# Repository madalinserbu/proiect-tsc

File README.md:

# OpenBook
Proiect TSC - Serbu Ovidiu Madalin

## Block Diagram

## Components

- **Microcontroller:** ESP32-C6 with integrated Wi-Fi 6 and Bluetooth 5 — responsible for core processing, communication, and power management.
- **Display:** 800×480 resolution e-Paper (e-Ink) display interfaced via SPI — ideal for low-power, high-visibility content rendering.
- **Sensors:** BME688 environmental sensor (temperature, humidity, pressure, air quality) connected through I2C.
- **Power Supply:** 2500mAh LiPo battery with USB-C charging and integrated fuel gauge for real-time battery monitoring.
- **Storage:** MicroSD card slot for storing e-books and other resources, communicating via SPI.
- **Real-Time Clock:** DS3231 RTC module with battery backup for accurate timekeeping even during power loss.
- **User Inputs:** 3 buttons (connected via GPIO) for navigation and control.
- **Expansion Options:** QWIIC/Stemma QT connector for easy integration of additional sensors or modules.

## Bill Of Materials

|                                   name                                   	|        value       	| description                                                           	| quantity 	|                                                                                                                                                     link                                                                                                                                                    	| datasheet                                                                                                                           	|
|:------------------------------------------------------------------------:	|:------------------:	|-----------------------------------------------------------------------	|:--------:	|:-----------------------------------------------------------------------------------------------------------------------------------------------------------------------------------------------------------------------------------------------------------------------------------------------------------:	|-------------------------------------------------------------------------------------------------------------------------------------	|
| LED1                                                                     	|          -         	| LED                                                                   	| 1        	| [link](https://www.niden.ro/led-uri-smd/4560-led-smd-0603-alb-rece.html)                                                                                                                                                                                                                                    	| [link](https://www.mouser.com/datasheet/2/423/LSM0603472V_(1)-1379786.pdf?srsltid=AfmBOoqdcB2pVIrWRImdZdFZcxn5SIjNLKeNM1u-ULY7G7UgiZHJYMAt)	|
| C18                                                                      	|      0.1uF/50V     	| CAPACITOR, European symbol                                            	| 1        	| [link](https://ro.mouser.com/ProductDetail/KEMET/C0402C104K4RAC7411?qs=GedzDrHbfJPMv36lRRfk4g%3D%3D)                                                                                                                                                                                                                	| [link](https://ro.mouser.com/datasheet/2/447/KEM_C1002_X7R_SMD-3316098.pdf)                                                                 	|
| R5                                                                       	|        0.47        	| RESISTOR, European symbol                                             	| 1        	| [link](https://ro.mouser.com/ProductDetail/ROHM-Semiconductor/SFR01MZPJ471?qs=sGAEpiMZZMtlubZbdhIBIONtIqra%2FA5YbUieG7R0owU%3D)                                                                                                                                                                                     	| [link](https://fscdn.rohm.com/en/products/databook/datasheet/passive/resistor/chip_resistor/sfr-e.pdf)                                      	|
| R1                                                                       	|        100K        	| RESISTOR, European symbol                                             	| 1        	| [link](https://ro.mouser.com/ProductDetail/Bourns/CR0402-FX-1003GLF?qs=URDPQ%2Fj0cz1ZruPSJQ7fsA%3D%3D&utm_id=6470900573&utm_source=google&utm_medium=cpc&utm_marketing_tactic=emeacorp&gad_source=1&gclid=CjwKCAjwzMi_BhACEiwAX4YZUExf8o5xv9o__WAln9moW8yaWJv0M179-dCfAxoyQP6_ulvhYGGM9xoCahIQAvD_BwE)              	| [link](https://ro.mouser.com/datasheet/2/54/cr-1858361.pdf)                                                                                 	|
| C1, C5, C21, C22, C23, C25, C26, C27                                     	|        100nF       	| CAPACITOR, European symbol                                            	| 8        	| [link](https://ro.mouser.com/ProductDetail/KEMET/C0402C104K4RAC7411?qs=GedzDrHbfJPMv36lRRfk4g%3D%3D)                                                                                                                                                                                                                	| [link](https://ro.mouser.com/datasheet/2/447/KEM_C1002_X7R_SMD-3316098.pdf)                                                                 	|
| C2                                                                       	|        100uF       	| POLARIZED CAPACITOR, European symbol                                  	| 1        	| [link](https://ro.mouser.com/ProductDetail/KEMET/T491B107M006AT?qs=U312oeP%2FpiHOgyk6KO2m0g%3D%3D)                                                                                                                                                                                                                  	| [link](https://ro.mouser.com/datasheet/2/447/KEM_T2005_T491-3316937.pdf)                                                                    	|
| R18                                                                      	|         10K        	| RESISTOR, European symbol                                             	| 1        	| [link](https://ro.mouser.com/ProductDetail/Vishay-Dale/CRCW040210K0FKEDC?qs=E3Y5ESvWgWPiNLcGzwCGPg%3D%3D)                                                                                                                                                                                                           	| [link](https://www.vishay.com/docs/28773/crcwce3.pdf)                                                                                       	|
| R6, R10, R11, R12, R13, R14, R15, R16, R19, R20, R21, R22, R23, R24, R25 	|         10k        	| RESISTOR, European symbol                                             	| 15       	| [link](https://ro.mouser.com/ProductDetail/Vishay-Dale/CRCW040210K0FKEDC?qs=E3Y5ESvWgWPiNLcGzwCGPg%3D%3D)                                                                                                                                                                                                           	| [link](https://www.vishay.com/docs/28773/crcwce3.pdf)                                                                                       	|
| C7                                                                       	|        10uF        	| CAPACITOR, European symbol                                            	| 1        	| [link](https://ro.mouser.com/ProductDetail/KEMET/C0402C106M7PAC7867?qs=kZJHmUDErizJnkDIcqVWRQ%3D%3D)                                                                                                                                                                                                                	| [link](https://ro.mouser.com/datasheet/2/447/KEM_C1006_X5R_SMD-3316465.pdf)                                                                 	|
| J1                                                                       	|          -         	| Micro SD Card Socket, Push-Push Type, Top   Mount, SMT, H=1.83mm, 10u 	| 1        	| [link](https://www.digikey.ro/en/products/detail/attend-technology/112A-TAAR-R03/17633923)                                                                                                                                                                                                                          	| [link](https://www.attend.com.tw/data/download/file/112A-TAAR-R03_Spec.pdf)                                                                 	|
| R17                                                                      	|         15         	| RESISTOR, European symbol                                             	| 1        	| [link](https://www.soselectronic.com/ro-ro/products/yageo/r0402-5-15-r-rc0402jr-0715rl-1-81614)                                                                                                                                                                                                                     	| [link](https://cdn.soselectronic.com/productdata/4b/af/65353ac1/r0402-1-1-5-k-rc0402fr-071k5l-1.pdf)                                        	|
| C24                                                                      	|         1uF        	| CAPACITOR, European symbol                                            	| 1        	| [link](https://ro.mouser.com/ProductDetail/KEMET/C0402C105Z9VACTU?qs=gt1LBUVyoHlQieoJt4iw1w%3D%3D)                                                                                                                                                                                                                  	| [link](https://ro.mouser.com/datasheet/2/447/KEM_C1005_Y5V_SMD-3316374.pdf)                                                                 	|
| C11, C12, C13, C14, C15, C16, C17, C19, C20                              	|       1uF/50V      	| CAPACITOR, European symbol                                            	| 9        	| [link](https://ro.mouser.com/ProductDetail/KEMET/C0402C105Z9VACTU?qs=gt1LBUVyoHlQieoJt4iw1w%3D%3D)                                                                                                                                                                                                                  	| [link](https://ro.mouser.com/datasheet/2/447/KEM_C1005_Y5V_SMD-3316374.pdf)                                                                 	|
| R7                                                                       	|         2.2        	| RESISTOR, European symbol                                             	| 1        	| [link](https://ro.mouser.com/ProductDetail/Panasonic/ERJ-PA2J2R2X?qs=sGAEpiMZZMtlubZbdhIBIKn8wLs5z3UnO%252BN6Zqj8Y2A%3D)                                                                                                                                                                                            	| [link](https://industrial.panasonic.com/cdbs/www-data/pdf/RDO0000/AOA0000C331.pdf)                                                          	|
| R8                                                                       	|         200        	| RESISTOR, European symbol                                             	| 1        	| [link](https://ro.mouser.com/ProductDetail/Vishay-Thin-Film/PNM0402E2000BSTS?qs=sGAEpiMZZMvdGkrng054t2cqbZCzJY7NtycrwNLdAiqcSryq%252B1Rhtw%3D%3D)                                                                                                                                                                   	| [link](https://www.vishay.com/docs/60057/pnm.pdf)                                                                                           	|
| Q1, Q3                                                                   	| 20V/4.2A/52mO/1.4W 	| P-channel MOSFETs                                                     	| 2        	| [link](https://www.digikey.ro/en/products/detail/vishay-siliconix/SI1308EDL-T1-GE3/4876435?utm_campaign=buynow&utm_medium=aggregator&utm_source=snapeda)                                                                                                                                                            	| [link](https://www.vishay.com/docs/63399/si1308edl.pdf)                                                                                     	|
| R9                                                                       	|         2k         	| RESISTOR, European symbol                                             	| 1        	| [link](https://ro.mouser.com/ProductDetail/Vishay-Dale/CRCW04022K00FKEE?qs=raETa%252B32nO8lGcRW9MjUBA%3D%3D)                                                                                                                                                                                                        	| [link](https://www.vishay.com/docs/20035/dcrcwe3.pdf)                                                                                       	|
| C6, C9, C10                                                              	|        4.7uF       	| CAPACITOR, European symbol                                            	| 3        	| [link](https://ro.mouser.com/ProductDetail/KEMET/C0402C475K8PACTU?qs=ulEaXIWI0c9ebKRT3r3htg%3D%3D)                                                                                                                                                                                                                  	| [link](https://ro.mouser.com/datasheet/2/447/KEM_C1006_X5R_SMD-3316465.pdf)                                                                 	|
| C3, C4                                                                   	|        4.7uF       	| CAPACITOR, European symbol                                            	| 2        	| [link](https://ro.mouser.com/ProductDetail/KEMET/C0402C475K8PACTU?qs=ulEaXIWI0c9ebKRT3r3htg%3D%3D)                                                                                                                                                                                                                  	| [link](https://ro.mouser.com/datasheet/2/447/KEM_C1006_X5R_SMD-3316465.pdf)                                                                 	|
| C8                                                                       	|      4.7uF/25V     	| CAPACITOR, European symbol                                            	| 1        	| [link](https://ro.mouser.com/ProductDetail/KEMET/C0402C475K8PACTU?qs=ulEaXIWI0c9ebKRT3r3htg%3D%3D)                                                                                                                                                                                                                  	| [link](https://ro.mouser.com/ProductDetail/KEMET/C0402C475K8PACTU?qs=ulEaXIWI0c9ebKRT3r3htg%3D%3D)                                          	|
| D3                                                                       	|      4.7uF/25V     	| ON SEMICONDUCTOR - MBR0530 - DIODE,   SCHOTTKY, 0.5A, 30V, SOD-123    	| 1        	| [link](https://www.snapeda.com/parts/MBR0530/Onsemi/view-part/?ref=eda)                                                                                                                                                                                                                                             	| [link](https://www.snapeda.com/parts/MBR0530/ON%20Semiconductor/datasheet/)                                                                 	|
| R3, R4                                                                   	|         5k1        	| RESISTOR, European symbol                                             	| 2        	| [link](https://www.gme.cz/v/1484336/yageo-r0402-5k1-006w-1-smd-rezistor?srsltid=AfmBOooJFe0JuMtJCHsiAAMzt535X2PaRQWliIdlncts6E1iAX--2xYh)                                                                                                                                                                           	| [link](https://img.gme.cz/files/eshop_data/eshop_data/7/984-017/dsh.984-017.1.pdf)                                                          	|
| L1                                                                       	|        68uH        	| coil                                                                  	| 1        	| [link](https://ro.mouser.com/ProductDetail/Wurth-Elektronik/744043680?qs=PGXP4M47uW6VkZq%252BkzjrHA%3D%3D)                                                                                                                                                                                                          	| [link](https://www.we-online.com/components/products/datasheet/744043680.pdf)                                                               	|
| IC2                                                                      	|          -         	| Voltage Detector with Adjustable Delay                                	| 1        	| [link](https://ro.mouser.com/ProductDetail/ROHM-Semiconductor/BD5229G-TR?qs=4kLU8WoGk0vvnhrrYwdszw%3D%3D)                                                                                                                                                                                                           	| [link](https://fscdn.rohm.com/en/products/databook/datasheet/ic/power/voltage_detector/bd52xxg-e.pdf)                                       	|
| BOOT_BUTTON, CHANGE_BUTTON, RESET_BUTTON                                 	|          -         	| Button                                                                	| 3        	| [link](https://ro.mouser.com/ProductDetail/CK/PTS841-GK-SMTR-LFS?qs=d0WKAl%252BL4KbAtAqJT9yhkg%3D%3D)                                                                                                                                                                                                               	| [link](https://www.ckswitches.com/media/2805/pts841.pdf)                                                                                    	|
| C28                                                                      	|          -         	| Cap 0.011F 3.3V 1210 Flat                                             	| 1        	| [link](https://www.snapeda.com/parts/CPH3225A/Seiko+Instruments/view-part/?ref=eda)                                                                                                                                                                                                                                 	| [link](https://www.snapeda.com/parts/CPH3225A/Seiko%20Instruments/datasheet/)                                                               	|
| U5                                                                       	|          -         	| Real Time Clock Serial 16-Pin SOIC W   T/R                            	| 1        	| [link](https://www.snapeda.com/parts/DS3231SN%23/Analog+Devices/view-part/?ref=eda)                                                                                                                                                                                                                                 	| [link](https://www.snapeda.com/parts/DS3231SN%23/Analog%20Devices/datasheet/)                                                               	|
| U2                                                                       	|          -         	| ESP32                                                                 	| 1        	| [link](https://www.snapeda.com/parts/ESP32-C6-WROOM-1-N8/Espressif+Systems/view-part/?ref=eda)                                                                                                                                                                                                                      	| [link](https://www.snapeda.com/parts/ESP32-C6-WROOM-1-N8/Espressif%20Systems/datasheet/)                                                    	|
| R2                                                                       	|          -         	| VARISTOR                                                              	| 1        	| [link](https://www.digikey.ro/en/products/detail/epcos-tdk-electronics/B72580T0110K062/15903564)                                                                                                                                                                                                                    	| [link](https://www.tdk-electronics.tdk.com/inf/75/db/CTVS_14/Standard_series.pdf)                                                           	|
| D1, D6                                                                   	|          -         	| Schottky Barrier Rectifier Diode                                      	| 2        	| [link](https://eu.mouser.com/ProductDetail/KYOCERA-AVX/SD0805S020S1R0?qs=jCA%252BPfw4LHbpkAoSnwrdjw%3D%3D&srsltid=AfmBOoos7vAXHpuNsFyDZDH2ms56jfFYgACPLwGeQRLBDVu-QQCPVRyy)                                                                                                                                         	| [link](https://ro.mouser.com/datasheet/2/40/schottky-3165252.pdf)                                                                           	|
| U3                                                                       	|          -         	| Integrated Environmental Unit                                         	| 1        	| [link](https://ro.mouser.com/ProductDetail/Bosch-Sensortec/BME680?qs=v271MhAjFHjo0yA%2FC4OnDQ%3D%3D)                                                                                                                                                                                                                	| [link](https://ro.mouser.com/datasheet/2/783/BST_BME680_DS001-1509608.pdf)                                                                  	|
| U1                                                                       	|          -         	| MCP73831T Li-Ion, Li-Pol Controller                                   	| 1        	| [link](https://eu.mouser.com/ProductDetail/Microchip-Technology/MCP73831T-2ACI-OT?qs=yUQqVecv4qvbBQBGbHx0Mw%3D%3D&utm_id=20109199409&utm_source=google&utm_medium=cpc&utm_marketing_tactic=emeacorp&gad_source=1&gclid=CjwKCAjwzMi_BhACEiwAX4YZUFXFfoOvOVw-rJ3AqbhBnSMrJwio_-4FjBZgwNJVbUQHlwwnAKDqhBoCYr4QAvD_BwE) 	| [link](https://ro.mouser.com/datasheet/2/268/MCP73831_Family_Data_Sheet_DS20001984H-3441711.pdf)                                            	|
| J3                                                                       	|          -         	|  (0.50mm) Surface Mount, Right Angle                                  	| 1        	| [link](https://ro.mouser.com/ProductDetail/Hirose-Connector/FH34SRJ-24S-0.5SH99?qs=vcbW%252B4%252BSTIpKBl5ap9J8Fw%3D%3D&_gl=1*l9suft*_ga*MTI5Mzc0MzA3OS4xNzQzODQ5MDQz*_ga_15W4STQT4T*MTc0Mzk1NTYyNy40LjAuMTc0Mzk1NTYyNy42MC4wLjA.)                                                                                  	| [link](https://ro.mouser.com/datasheet/2/185/FH34SRJ_24S_0_5SH_99__CL0580_1255_6_99_2DDrawing_0-1615044.pdf)                                	|
| U4                                                                       	|          -         	| 3µA 1-Cell/2-Cell Fuel Gauge with ModelGauge                          	| 1        	| [link](https://www.snapeda.com/parts/MAX17048G+T10/Analog+Devices/view-part/?ref=eda)                                                                                                                                                                                                                               	| [link](https://www.snapeda.com/parts/MAX17048G+T10/Analog%20Devices/datasheet/)                                                             	|
| D4, D5                                                                   	|          -         	| DIODE,   SCHOTTKY, 0.5A, 30V, SOD-123                                 	| 2        	| [link](https://www.snapeda.com/parts/MBR0530/Onsemi/view-part/?ref=eda)                                                                                                                                                                                                                                             	| [link](https://www.snapeda.com/parts/MBR0530/ON%20Semiconductor/datasheet/)                                                                 	|
| D7, D8, D9, D10, D11, D12                                                	|          -         	| Ipp Tvs Diode                                                         	| 6        	| [link](https://www.snapeda.com/parts/PGB1010603MR/Littelfuse/view-part/?ref=eda)                                                                                                                                                                                                                                    	| [link](https://www.snapeda.com/parts/PGB1010603MR/Littelfuse%20Inc./datasheet/)                                                             	|
| J4                                                                       	|          -         	| SparkFun I2C Standard Qwiic Connector                                 	| 1        	| [link](https://www.sparkfun.com/qwiic-jst-connector-smd-4-pin-horizontal.html)                                                                                                                                                                                                                                      	| [link](https://cdn.sparkfun.com/assets/parts/1/2/2/8/9/Qwiic_Connector_Datasheet.pdf)                                                       	|
| J2                                                                       	|          -         	| CONN USB 2.0 TYPE-C R/A SMT                                           	| 1        	| [link](https://ro.mouser.com/ProductDetail/GCT/USB4110-GF-A?qs=KUoIvG%2F9IlYiZvIXQjyJeA%3D%3D)                                                                                                                                                                                                                      	| [link](https://ro.mouser.com/datasheet/2/837/GCT_USB4110_Product_Drawing___20k_cycles-3455479.pdf)                                          	|
| Q2                                                                       	|          -         	| MOSFET N-Ch 30V 1.5A                                                  	| 1        	| [link](https://www.snapeda.com/parts/SI1308EDL-T1-GE3/Vishay+Siliconix/view-part/?ref=eda)                                                                                                                                                                                                                          	| [link](https://www.snapeda.com/parts/SI1308EDL-T1-GE3/Vishay%20Siliconix/datasheet/)                                                        	|
| D2                                                                       	|          -         	| Low Cap. ESD Protection Auto SOT-23-6                                 	| 1        	| [link](https://www.snapeda.com/parts/USBLC6-2SC6Y/STMicroelectronics/view-part/?ref=eda)                                                                                                                                                                                                                            	| [link](https://www.snapeda.com/parts/USBLC6-2SC6Y/STMicroelectronics/datasheet/)                                                            	|
| U6                                                                       	|          -         	| FLASH - NOR Memory IC 512Mb                                           	| 1        	| [link](https://www.snapeda.com/parts/W25Q512JVEIQ/Winbond+Electronics/view-part/?ref=eda)                                                                                                                                                                                                                           	| [link](https://www.snapeda.com/parts/W25Q512JVEIQ/Winbond%20Electronics/datasheet/)                                                         	|
| IC1                                                                      	|          -         	| LDO Voltage Regulator                                                 	| 1        	| [link](https://ro.mouser.com/ProductDetail/Torex-Semiconductor/XC6220A331MR-G?qs=AsjdqWjXhJ8ZSWznL1J0gg%3D%3D&utm_id=6470900573&utm_source=google&utm_medium=cpc&utm_marketing_tactic=emeacorp&gad_source=1&gclid=CjwKCAjwzMi_BhACEiwAX4YZUHiB3kDs66vv29tGnRc8y1huoaOvdBlKkwXVy8QKs7T5wBQH4NGZUxoCU5wQAvD_BwE)      	| [link](https://ro.mouser.com/datasheet/2/760/xc6220-3371556.pdf)                                                                            	|

## ESP32-C6 Pins

| Connection      | Pin            | Description                                                               |
|-----------------|----------------|---------------------------------------------------------------------------|
| **RESET**       | EN             | Reset button for initiating a reset sequence                              |
| **INT_RTC**     | IO0            | Interrupt signal for the RTC                                              |
| **32KHZ**       | IO1            | Input for 32kHz clock signal                                              |
| **MISO**        | IO2            | Master In Slave Out for communication between the microcontroller, Flash, SD Card, and display |
| **EPD_BUSY**    | IO3            | Signal indicating if the display is busy                                  |
| **SS_SD**       | IO4            | Chip select for the SD card                                               |
| **EPD_DC**      | IO5            | Display data/command control pin                                          |
| **SCK**         | IO6            | SPI clock for synchronizing data transfers                                |
| **MOSI**        | IO7            | Master Out Slave In for data transmission between the microcontroller, Flash, SD card, and display |
| **3V3**         | IO8            | 3.3V power supply                                                          |
| **IO/BOOT**     | IO9            | Boot button to trigger boot process                                       |
| **EPD_CS**      | IO10           | Chip select for the display                                               |
| **FLASH_CS**    | IO11           | Chip select for the Flash memory                                          |
| **USB_D-**      | IO12           | USB data negative for communication                                       |
| **USB_D+**      | IO13           | USB data positive for communication                                       |
| **IO/CHANGE**   | IO15           | Button to trigger a change action                                         |
| **TX (UART)**   | TXD0 / GPIO16  | Serial transmitter for UART communication                                 |
| **RX (UART)**   | RXD0 / GPIO17  | Serial receiver for UART communication                                    |
| **RTC_RST**     | IO18           | External reset for the RTC module                                         |
| **I2C_PW**      | IO19           | Power control signal for I2C devices                                      |
| **EPD_3V3_C**   | IO20           | 3.3V power supply for the display                                         |
| **SDA (I2C)**   | IO21           | Data line for I2C communication (e.g., RTC, BME688, Battery Gauge)       |
| **SCL (I2C)**   | IO22           | Clock line for I2C synchronization                                        |
| **EPD_RST**     | IO23           | Reset signal for the display                                              |
| **3V3**         | 3V3            | 3.3V power line                                                           |
| **GND**         | GND            | Ground connection                                                         |

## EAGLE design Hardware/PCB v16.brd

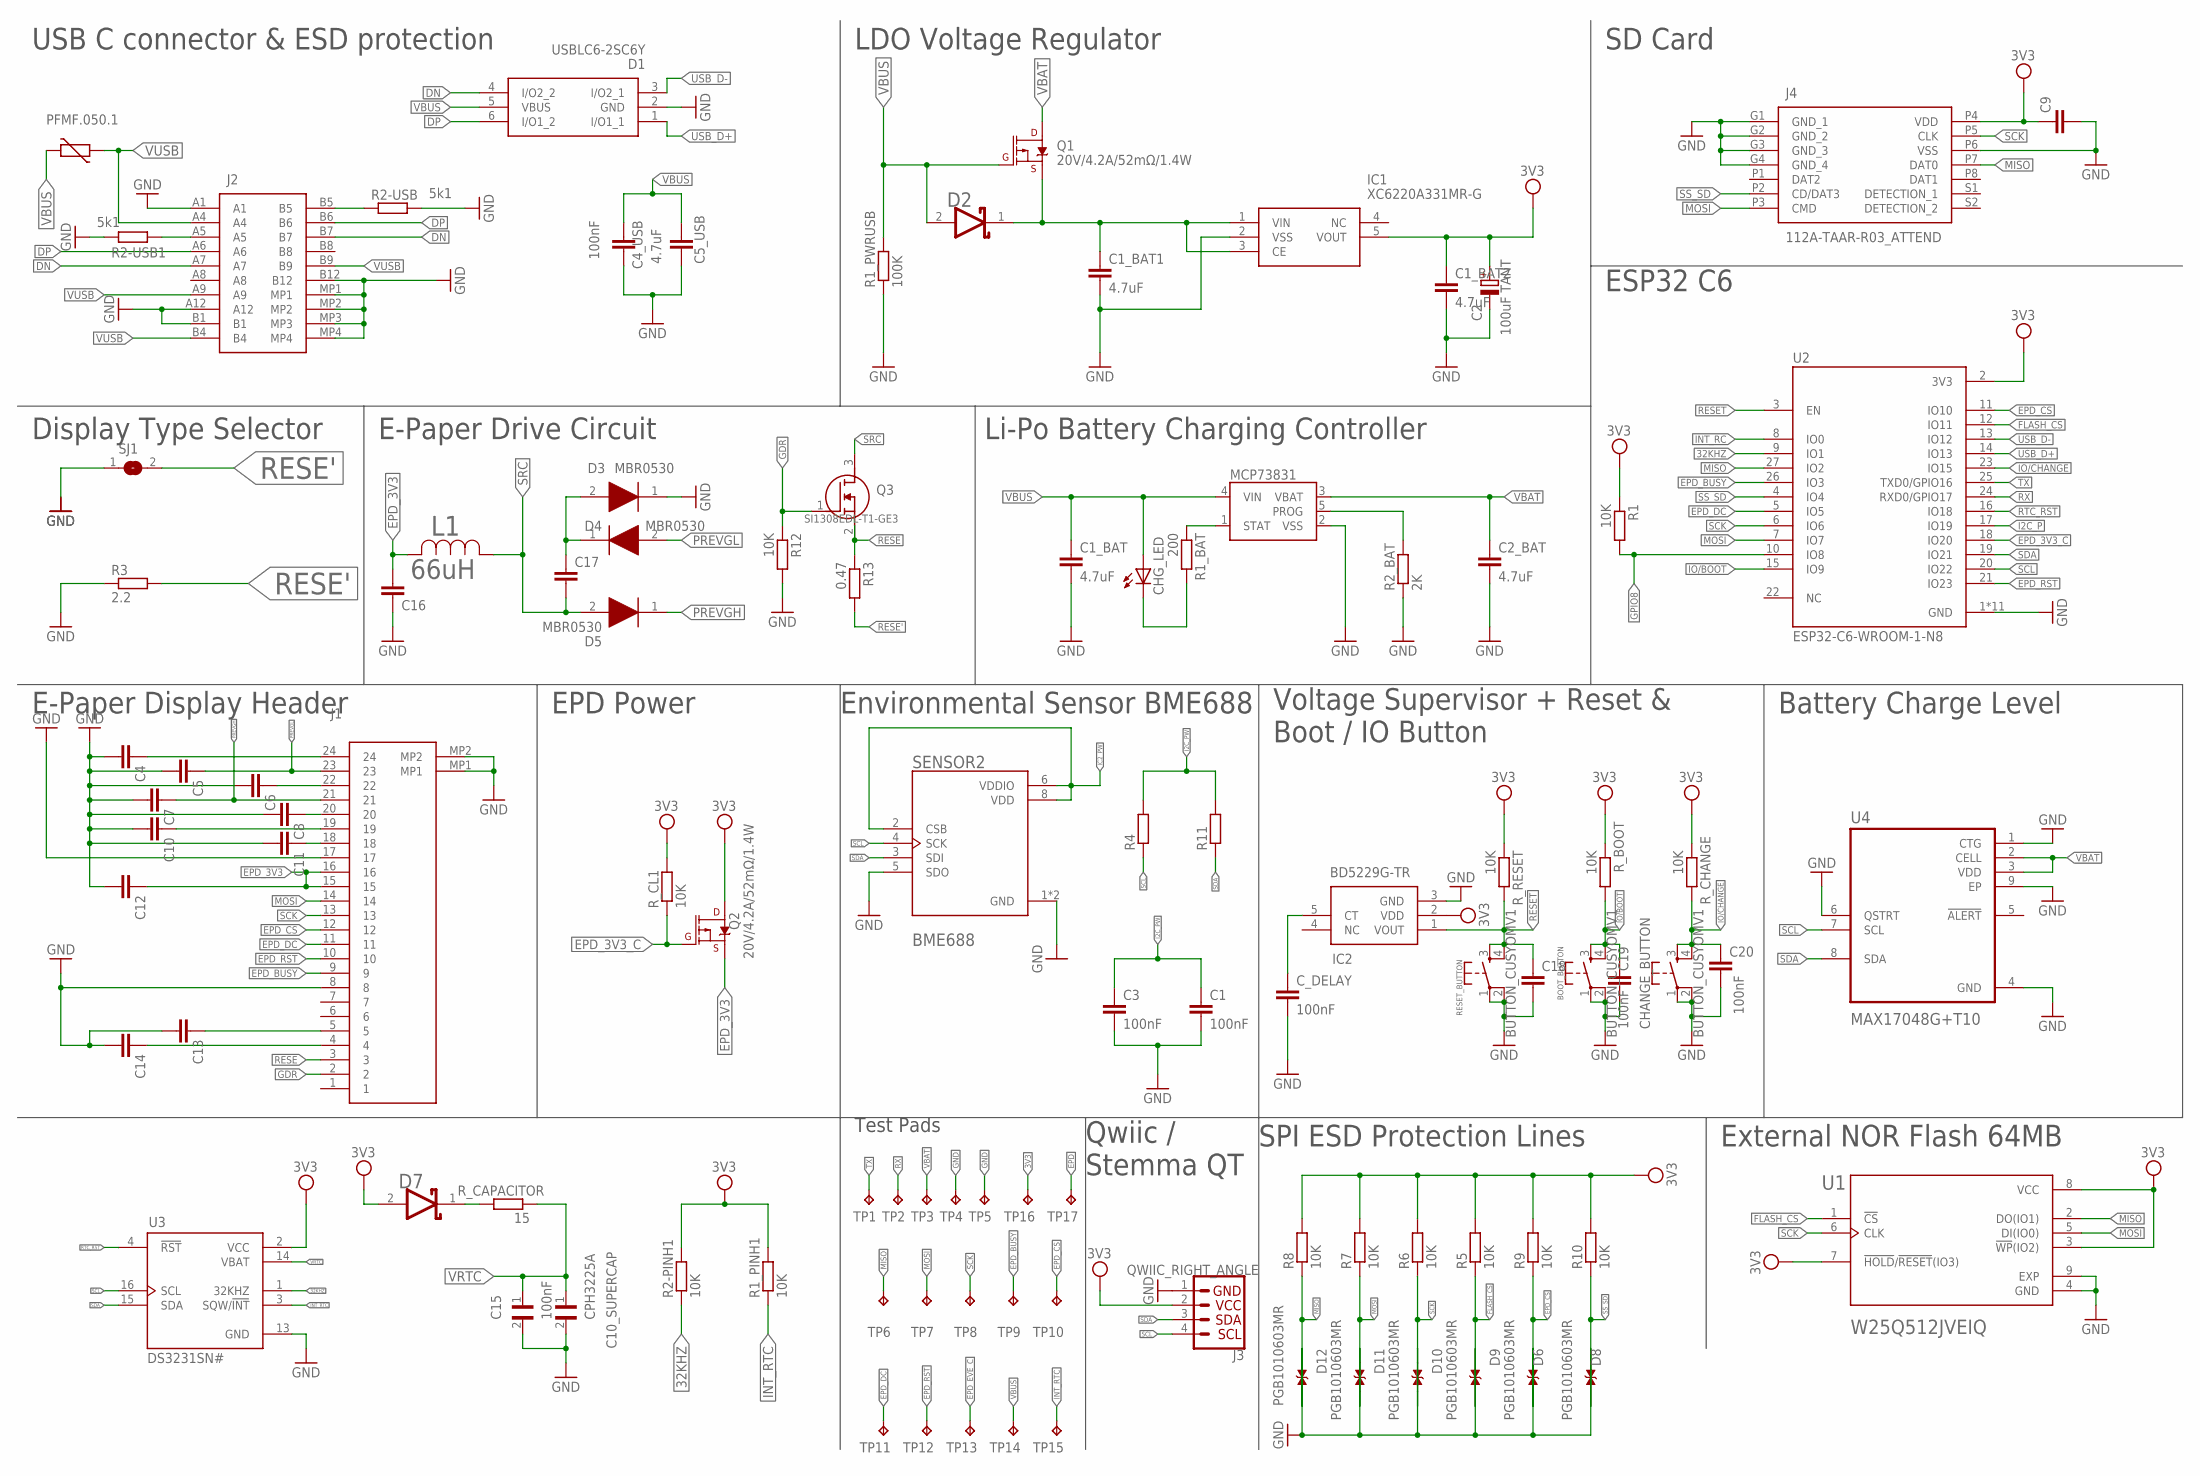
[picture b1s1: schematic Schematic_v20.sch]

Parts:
BOOT_BUTTON: BUTTON_CUSYOMV1; MYBUTTON
C1, C3, C4_USB, C19, C20: 100nF; ESP32_WROVER_EAGLE-LTSPICE_C0402
C1_BAT, C1_BAT1, C1_BAT2, C2_BAT, C5_USB: 4.7uF; ESP32_WROVER_EAGLE-LTSPICE_C0402
C2: 100uF TANT; RCL_CT3528
C4, C5, C6, C7, C8, C9, C10, C11, C12, C13, C14, C16, C17, C18: ESP32_WROVER_EAGLE-LTSPICE_CC0402; ESP32_WROVER_EAGLE-LTSPICE_C0402
C10_SUPERCAP: CPH3225A; CAPCP3225X100N
C15: 100nF; CAPCP3225X100N
CHANGE_BUTTON: BUTTON_CUSYOMV1; MYBUTTON
CHG_LED: ADAFRUIT_LEDCHIP-LED0603; ADAFRUIT_CHIP-LED0603
C_DELAY: 100nF; ESP32_WROVER_EAGLE-LTSPICE_C0402
D1: USBLC6-2SC6Y; SOT95P280X145-6N
D2: SD0805S020S1R0; ESP32_WROVER_AVX---SD0805S020S1R0_AVX_SD0805S020S1R0_0
D3, D4, D5: MBR0530; SOD3716X135N
D6, D8, D9, D10, D11, D12: PGB1010603MR; DIOC1608X36N
D7: ESP32_WROVER_AVX---SD0805S020S1R0_AVX_SD0805S020S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; ESP32_WROVER_AVX---SD0805S020S1R0_AVX_SD0805S020S1R0_0
IC1: XC6220A331MR-G; SOT95P280X120-5N
IC2: BD5229G-TR; SOT95P280X125-5N
J1: FH34SRJ-24S-0.5SH_99_; FH34SRJ24S05SH99
J2: SAMACSYS_PARTS_USB4110-GF-A; SAMACSYS_PARTS_USB4110GFA
J3: QWIIC_RIGHT_ANGLE; JST04_1MM_RA
J4: 112A-TAAR-R03_ATTEND; 112ATAARR03ATTEND
L1: 66uH; IND_4828-WE-TPC_WRE
MCP73831: ESP32_WROVER_SPARKFUN-IC-POWER_MCP73831; ESP32_WROVER_SPARKFUN-IC-POWER_SOT23-5
Q1, Q2: 20V/4.2A/52mΩ/1.4W; ESP32_WROVER_SPARKFUN-DISCRETESEMI_SOT23-3
Q3: SI1308EDL-T1-GE3; SOT65P210X110-3N
R1, R1_PINH1, R2-PINH1, R5, R6, R7, R8, R9, R10, R12: 10K; ESP32_WROVER_EAGLE-LTSPICE_R0402
R1_BAT: 200; ESP32_WROVER_EAGLE-LTSPICE_R0402
R1_PWRUSB: 100K; ESP32_WROVER_EAGLE-LTSPICE_R0402
R2: PFMF.050.1; ESP32C6_VARISTOR_CT/CN1812
R2-USB, R2-USB1: 5k1; ESP32_WROVER_EAGLE-LTSPICE_R0402
R2_BAT: 2K; ESP32_WROVER_EAGLE-LTSPICE_R0402
R3: 2.2; ESP32_WROVER_EAGLE-LTSPICE_R0402
R4, R11: ESP32_WROVER_EAGLE-LTSPICE_RR0402; ESP32_WROVER_EAGLE-LTSPICE_R0402
R13: 0.47; ESP32_WROVER_EAGLE-LTSPICE_R0402
RESET_BUTTON: BUTTON_CUSYOMV1; MYBUTTON
R_BOOT: 10K; ESP32_WROVER_EAGLE-LTSPICE_R0402
R_CAPACITOR: 15; ESP32_WROVER_EAGLE-LTSPICE_R0402
R_CHANGE: 10K; ESP32_WROVER_EAGLE-LTSPICE_R0402
R_CL1: 10K; ESP32_WROVER_EAGLE-LTSPICE_R0402
R_RESET: 10K; ESP32_WROVER_EAGLE-LTSPICE_R0402
SENSOR2: BME688; ESP32_WROVER_BME680_PSON80P300X300X100-8N
SJ1: SJ
TP1, TP2, TP3, TP4, TP5, TP6, TP7, TP8, TP9, TP10, TP11, TP12, TP13, TP14, TP15, TP16, TP17: TPTP20R; TP20R
U1: W25Q512JVEIQ; SON127P600X800X80-9N
U2: ESP32-C6-WROOM-1-N8; XCVR_ESP32-C6-WROOM-1-N8
U3: DS3231SN#; SOIC127P1032X265-16N
U4: MAX17048G+T10; SON50P200X200X80-9N

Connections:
3V3: C1_BAT2.1, C2.+, C9.1, D7.2 (ANODE), IC1.5 (VOUT), IC2.2 (VDD), J3.2, J4.P4 (VDD), Q2.3 (D), R1.1, R1_PINH1.2, R2-PINH1.2, R5.2, R6.2, R7.2, R8.2, R9.2, R10.2, R_BOOT.1, R_CHANGE.1, R_CL1.2, R_RESET.1, TP16.TP, U1.3 (!WP!(IO2)), U1.7 (!HOLD!/!RESET!(IO3)), U1.8 (VCC), U2.2 (3V3), U3.2 (VCC)
32KHZ: R2-PINH1.1, U2.9 (IO1), U3.1 (32KHZ)
DN: D1.4 (I/O2_2), J2.A7, J2.B7
DP: D1.6 (I/O1_2), J2.A6, J2.B6
EPD: TP17.TP
EPD_3V3: C12.1, C16.1, J1.15, J1.16, L1.2, Q2.2 (S)
EPD_3V3_C: Q2.1 (G), R_CL1.1, U2.18 (IO20)
EPD_BUSY: J1.9, TP9.TP, U2.26 (IO3)
EPD_CS: D6.2, J1.12, R9.1, TP10.TP, U2.11 (IO10)
EPD_DC: J1.11, TP11.TP, U2.5 (IO5)
EPD_EVE_C: TP13.TP
EPD_RST: J1.10, TP12.TP, U2.21 (IO23)
FLASH_CS: D9.2, R5.1, U1.1 (!CS), U2.12 (IO11)
GDR: J1.2, Q3.1 (G), R12.1
GND: BOOT_BUTTON.1, BOOT_BUTTON.2, C1.2, C1_BAT.2, C1_BAT1.2, C1_BAT2.2, C2.-, C2_BAT.2, C3.2, C4.2, C4_USB.2, C5.2, C5_USB.2, C6.2, C7.2, C8.2, C9.2, C10.2, C10_SUPERCAP.2, C11.2, C12.2, C13.2, C14.2, C15.2, C16.2, C18.2, C19.2, C20.2, CHANGE_BUTTON.1, CHANGE_BUTTON.2, C_DELAY.2, D1.2 (GND), D4.1 (K), D6.1, D8.1, D9.1, D10.1, D11.1, D12.1, IC1.2 (VSS), IC2.3 (GND), J1.8, J1.17, J1.MP1, J1.MP2, J2.A1, J2.A12, J2.B1, J2.B12, J2.MP1, J2.MP2, J2.MP3, J2.MP4, J3.1, J4.G1 (GND_1), J4.G2 (GND_2), J4.G3 (GND_3), J4.G4 (GND_4), J4.P6 (VSS), MCP73831.2 (VSS), R1_PWRUSB.1, R2-USB.2, R2-USB1.1, R2_BAT.1, R3.1, R12.2, RESET_BUTTON.1, RESET_BUTTON.2, SENSOR2.1 (GND), SENSOR2.5 (SDO), SENSOR2.7 (GND), SJ1.1, TP4.TP, TP5.TP, U1.4 (GND), U1.9 (EXP), U2.1 (GND), U2.28 (GND), U2.29_1 (GND), U2.29_2 (GND), U2.29_3 (GND), U2.29_4 (GND), U2.29_5 (GND), U2.29_6 (GND), U2.29_7 (GND), U2.29_8 (GND), U2.29_9 (GND), U3.13 (GND), U4.1 (CTG), U4.4 (GND), U4.6 (QSTRT), U4.9 (EP)
GPIO8: R1.2, U2.10 (IO8)
I2C_P: U2.17 (IO19)
I2C_PW: C1.1, C3.1, R4.2, R11.2
IC2_PW: SENSOR2.2 (CSB), SENSOR2.6 (VDDIO), SENSOR2.8 (VDD)
INT_RC: U2.8 (IO0)
INT_RTC: R1_PINH1.1, TP15.TP, U3.3 (SQW/!INT)
IO/BOOT: BOOT_BUTTON.3, BOOT_BUTTON.4, C19.1, R_BOOT.2, U2.15 (IO9)
IO/CHANGE: C20.1, CHANGE_BUTTON.3, CHANGE_BUTTON.4, R_CHANGE.2, U2.23 (IO15)
MISO: D12.2, J4.P7 (DAT0), R8.1, TP6.TP, U1.2 (DO(IO1)), U2.27 (IO2)
MOSI: D11.2, J1.14, J4.P3 (CMD), R7.1, TP7.TP, U1.5 (DI(IO0)), U2.7 (IO7)
unnamed: J2.A5, R2-USB1.2
unnamed: C4.1, J1.24
unnamed: C1_BAT1.1, D2.1 (CATHODE), IC1.1 (VIN), IC1.3 (CE), Q1.2 (S)
unnamed: CHG_LED.C, R1_BAT.2
unnamed: MCP73831.5 (PROG), R2_BAT.2
unnamed: J2.B5, R2-USB.1
unnamed: MCP73831.1 (STAT), R1_BAT.1
unnamed: D7.1 (CATHODE), R_CAPACITOR.2
unnamed: C6.1, J1.22
unnamed: C_DELAY.1, IC2.5 (CT)
unnamed: C8.1, J1.20
unnamed: C10.1, J1.19
unnamed: C11.1, J1.18
unnamed: C17.1, D3.1 (K), D4.2 (A)
unnamed: C13.1, J1.5
unnamed: C14.1, J1.4
PREVGH: C7.1, D5.1 (K), J1.21
PREVGL: C5.1, D3.2 (A), J1.23
RESE: J1.3, Q3.2 (S), R13.1
RESE': R3.2, R13.2, SJ1.2
RESET: C18.1, IC2.1 (VOUT), RESET_BUTTON.3, RESET_BUTTON.4, R_RESET.2, U2.3 (EN)
RTC_RST: U2.16 (IO18), U3.4 (!RST)
RX: TP2.TP, U2.24 (RXD0/GPIO17)
SCK: D10.2, J1.13, J4.P5 (CLK), R6.1, TP8.TP, U1.6 (CLK), U2.6 (IO6)
SCL: J3.4, R4.1, SENSOR2.4 (SCK), U2.20 (IO22), U3.16 (SCL), U4.7 (SCL)
SDA: J3.3, R11.1, SENSOR2.3 (SDI), U2.19 (IO21), U3.15 (SDA), U4.8 (SDA)
SRC: C17.2, D5.2 (A), L1.1, Q3.3 (D)
SS_SD: D8.2, J4.P2 (CD/DAT3), R10.1, U2.4 (IO4)
TX: TP1.TP, U2.25 (TXD0/GPIO16)
USB_D+: D1.1 (I/O1_1), U2.14 (IO13)
USB_D-: D1.3 (I/O2_1), U2.13 (IO12)
VBAT: C2_BAT.1, MCP73831.3 (VBAT), Q1.3 (D), TP3.TP, U4.2 (CELL), U4.3 (VDD)
VBUS: C1_BAT.1, C4_USB.1, C5_USB.1, CHG_LED.A, D1.5 (VBUS), D2.2 (ANODE), MCP73831.4 (VIN), Q1.1 (G), R1_PWRUSB.2, R2.1, TP14.TP
VRTC: C10_SUPERCAP.1, C15.1, R_CAPACITOR.1, U3.14 (VBAT)
VUSB: J2.A4, J2.A9, J2.B4, J2.B9, R2.2

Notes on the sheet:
USB C connector & ESD protection
SD Card
ESP32 C6
Battery Charge Level
External NOR Flash 64MB
SPI ESD Protection Lines
Qwiic / Stemma QT
Test Pads
LDO Voltage Regulator
Display Type Selector
Li-Po Battery Charging Controller
Environmental Sensor BME688
E-Paper Display Header
EPD Power
E-Paper Drive Circuit
Voltage Supervisor + Reset & Boot / IO Button

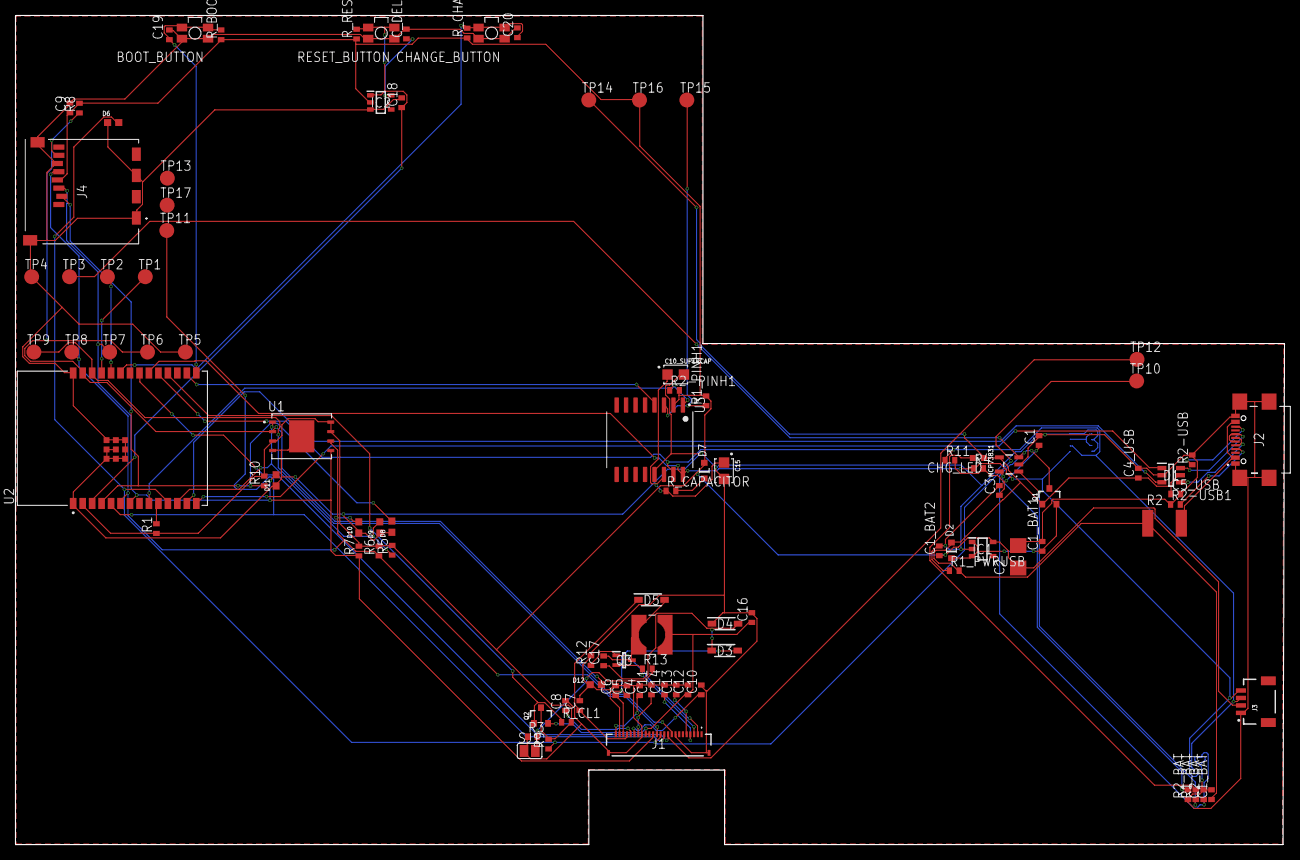
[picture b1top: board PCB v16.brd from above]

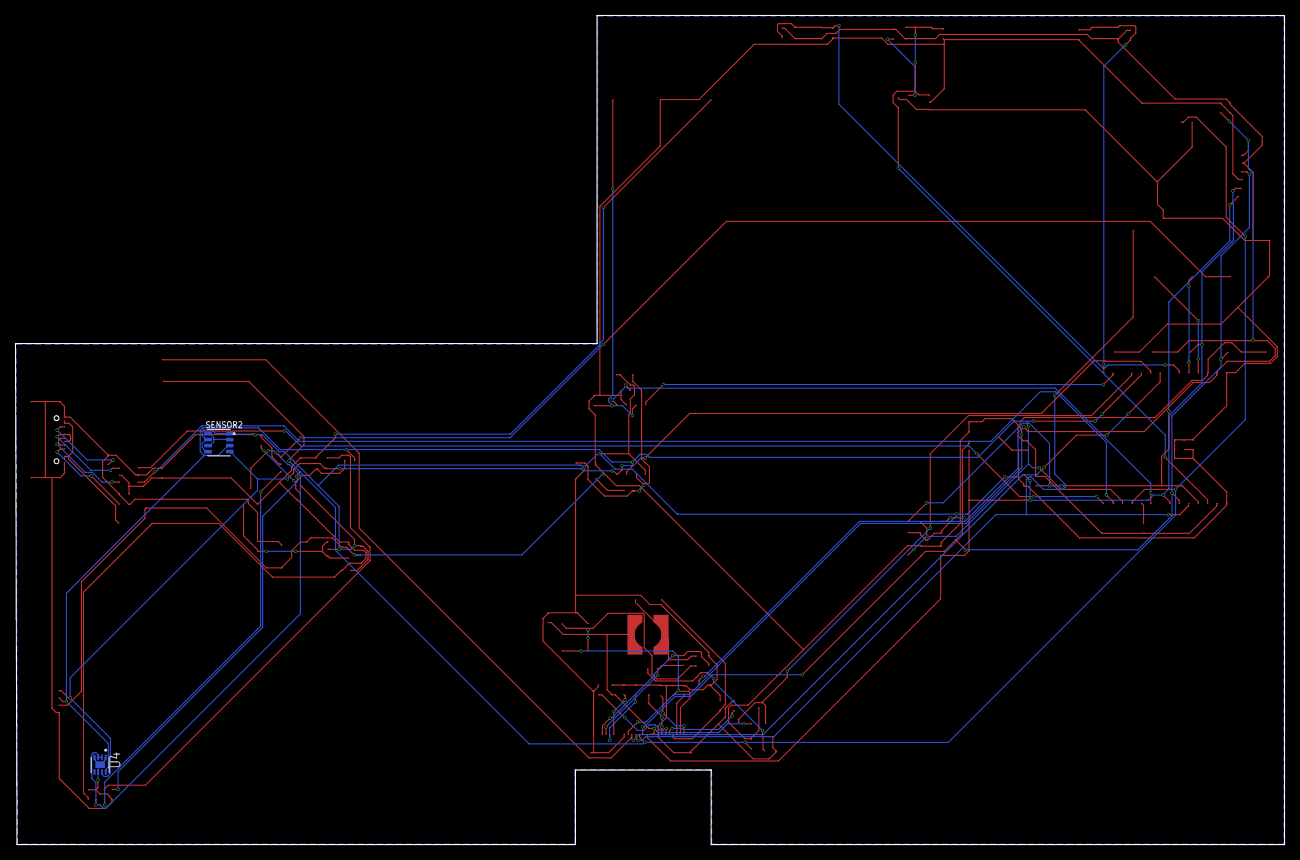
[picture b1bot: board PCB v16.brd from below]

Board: 2 copper layers, 170.2 x 111.2 mm, 103 parts (2 on the bottom side), 56 nets.

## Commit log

2025-04-06 Create LICENSE
2025-04-06 Added README

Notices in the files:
parts and their libraries:
COPYRIGHT: Copyright (C) 2024 Ultra Librarian. All rights reserved.
